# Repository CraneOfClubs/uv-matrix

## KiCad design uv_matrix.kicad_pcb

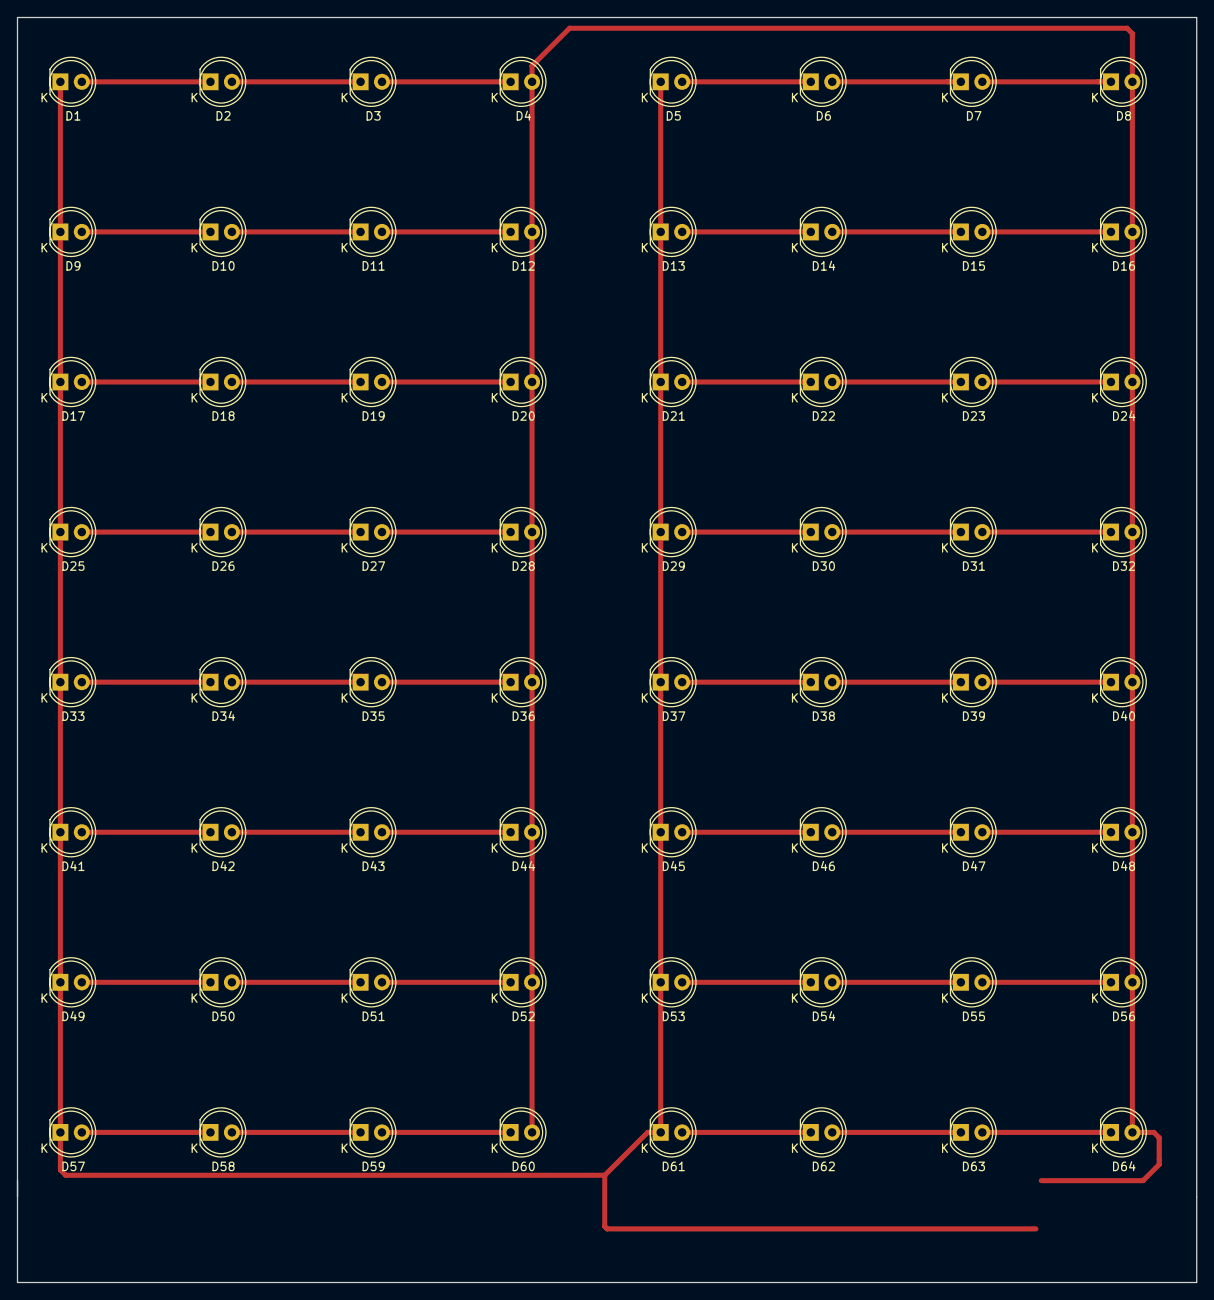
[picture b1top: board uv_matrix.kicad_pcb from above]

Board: 2 copper layers, 139.7 x 149.9 mm, 64 parts (0 on the bottom side), 50 nets.

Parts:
D1, D2, D3, D4, D5, D6, D7, D8, D9, D10, D11, D12, D13, D14, D15, D16, D17, D18, D19, D20, D21, D22, D23, D24, D25, D26, D27, D28, D29, D30, D31, D32, D33, D34, D35, D36, D37, D38, D39, D40, D41, D42, D43, D44, D45, D46, D47, D48, D49, D50, D51, D52, D53, D54, D55, D56, D57, D58, D59, D60, D61, D62, D63, D64: LED; LED-5MM

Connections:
+12V: D4.2, D8.2, D12.2, D16.2, D20.2, D24.2, D28.2, D32.2, D36.2, D40.2, D44.2, D48.2, D52.2, D56.2, D60.2, D64.2
GNDREF: D1.1, D5.1, D9.1, D13.1, D17.1, D21.1, D25.1, D29.1, D33.1, D37.1, D41.1, D45.1, D49.1, D53.1, D57.1, D61.1
unnamed: D1.2, D2.1
unnamed: D2.2, D3.1
unnamed: D3.2, D4.1
unnamed: D5.2, D6.1
unnamed: D6.2, D7.1
unnamed: D7.2, D8.1
unnamed: D9.2, D10.1
unnamed: D10.2, D11.1
unnamed: D11.2, D12.1
unnamed: D13.2, D14.1
unnamed: D14.2, D15.1
unnamed: D15.2, D16.1
unnamed: D17.2, D18.1
unnamed: D18.2, D19.1
unnamed: D19.2, D20.1
unnamed: D21.2, D22.1
unnamed: D22.2, D23.1
unnamed: D23.2, D24.1
unnamed: D25.2, D26.1
unnamed: D26.2, D27.1
unnamed: D27.2, D28.1
unnamed: D29.2, D30.1
unnamed: D30.2, D31.1
unnamed: D31.2, D32.1
unnamed: D33.2, D34.1
unnamed: D34.2, D35.1
unnamed: D35.2, D36.1
unnamed: D37.2, D38.1
unnamed: D38.2, D39.1
unnamed: D39.2, D40.1
unnamed: D41.2, D42.1
unnamed: D42.2, D43.1
unnamed: D43.2, D44.1
unnamed: D45.2, D46.1
unnamed: D46.2, D47.1
unnamed: D47.2, D48.1
unnamed: D49.2, D50.1
unnamed: D50.2, D51.1
unnamed: D51.2, D52.1
unnamed: D53.2, D54.1
unnamed: D54.2, D55.1
unnamed: D55.2, D56.1
unnamed: D57.2, D58.1
unnamed: D58.2, D59.1
unnamed: D59.2, D60.1
unnamed: D61.2, D62.1
unnamed: D62.2, D63.1
unnamed: D63.2, D64.1

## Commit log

2017-01-25 YOBA
2017-02-16 dgdgd
